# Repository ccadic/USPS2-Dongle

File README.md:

# USPS2-Dongle
ESP32S2 HID Keyboard Key
Still at prototype stage

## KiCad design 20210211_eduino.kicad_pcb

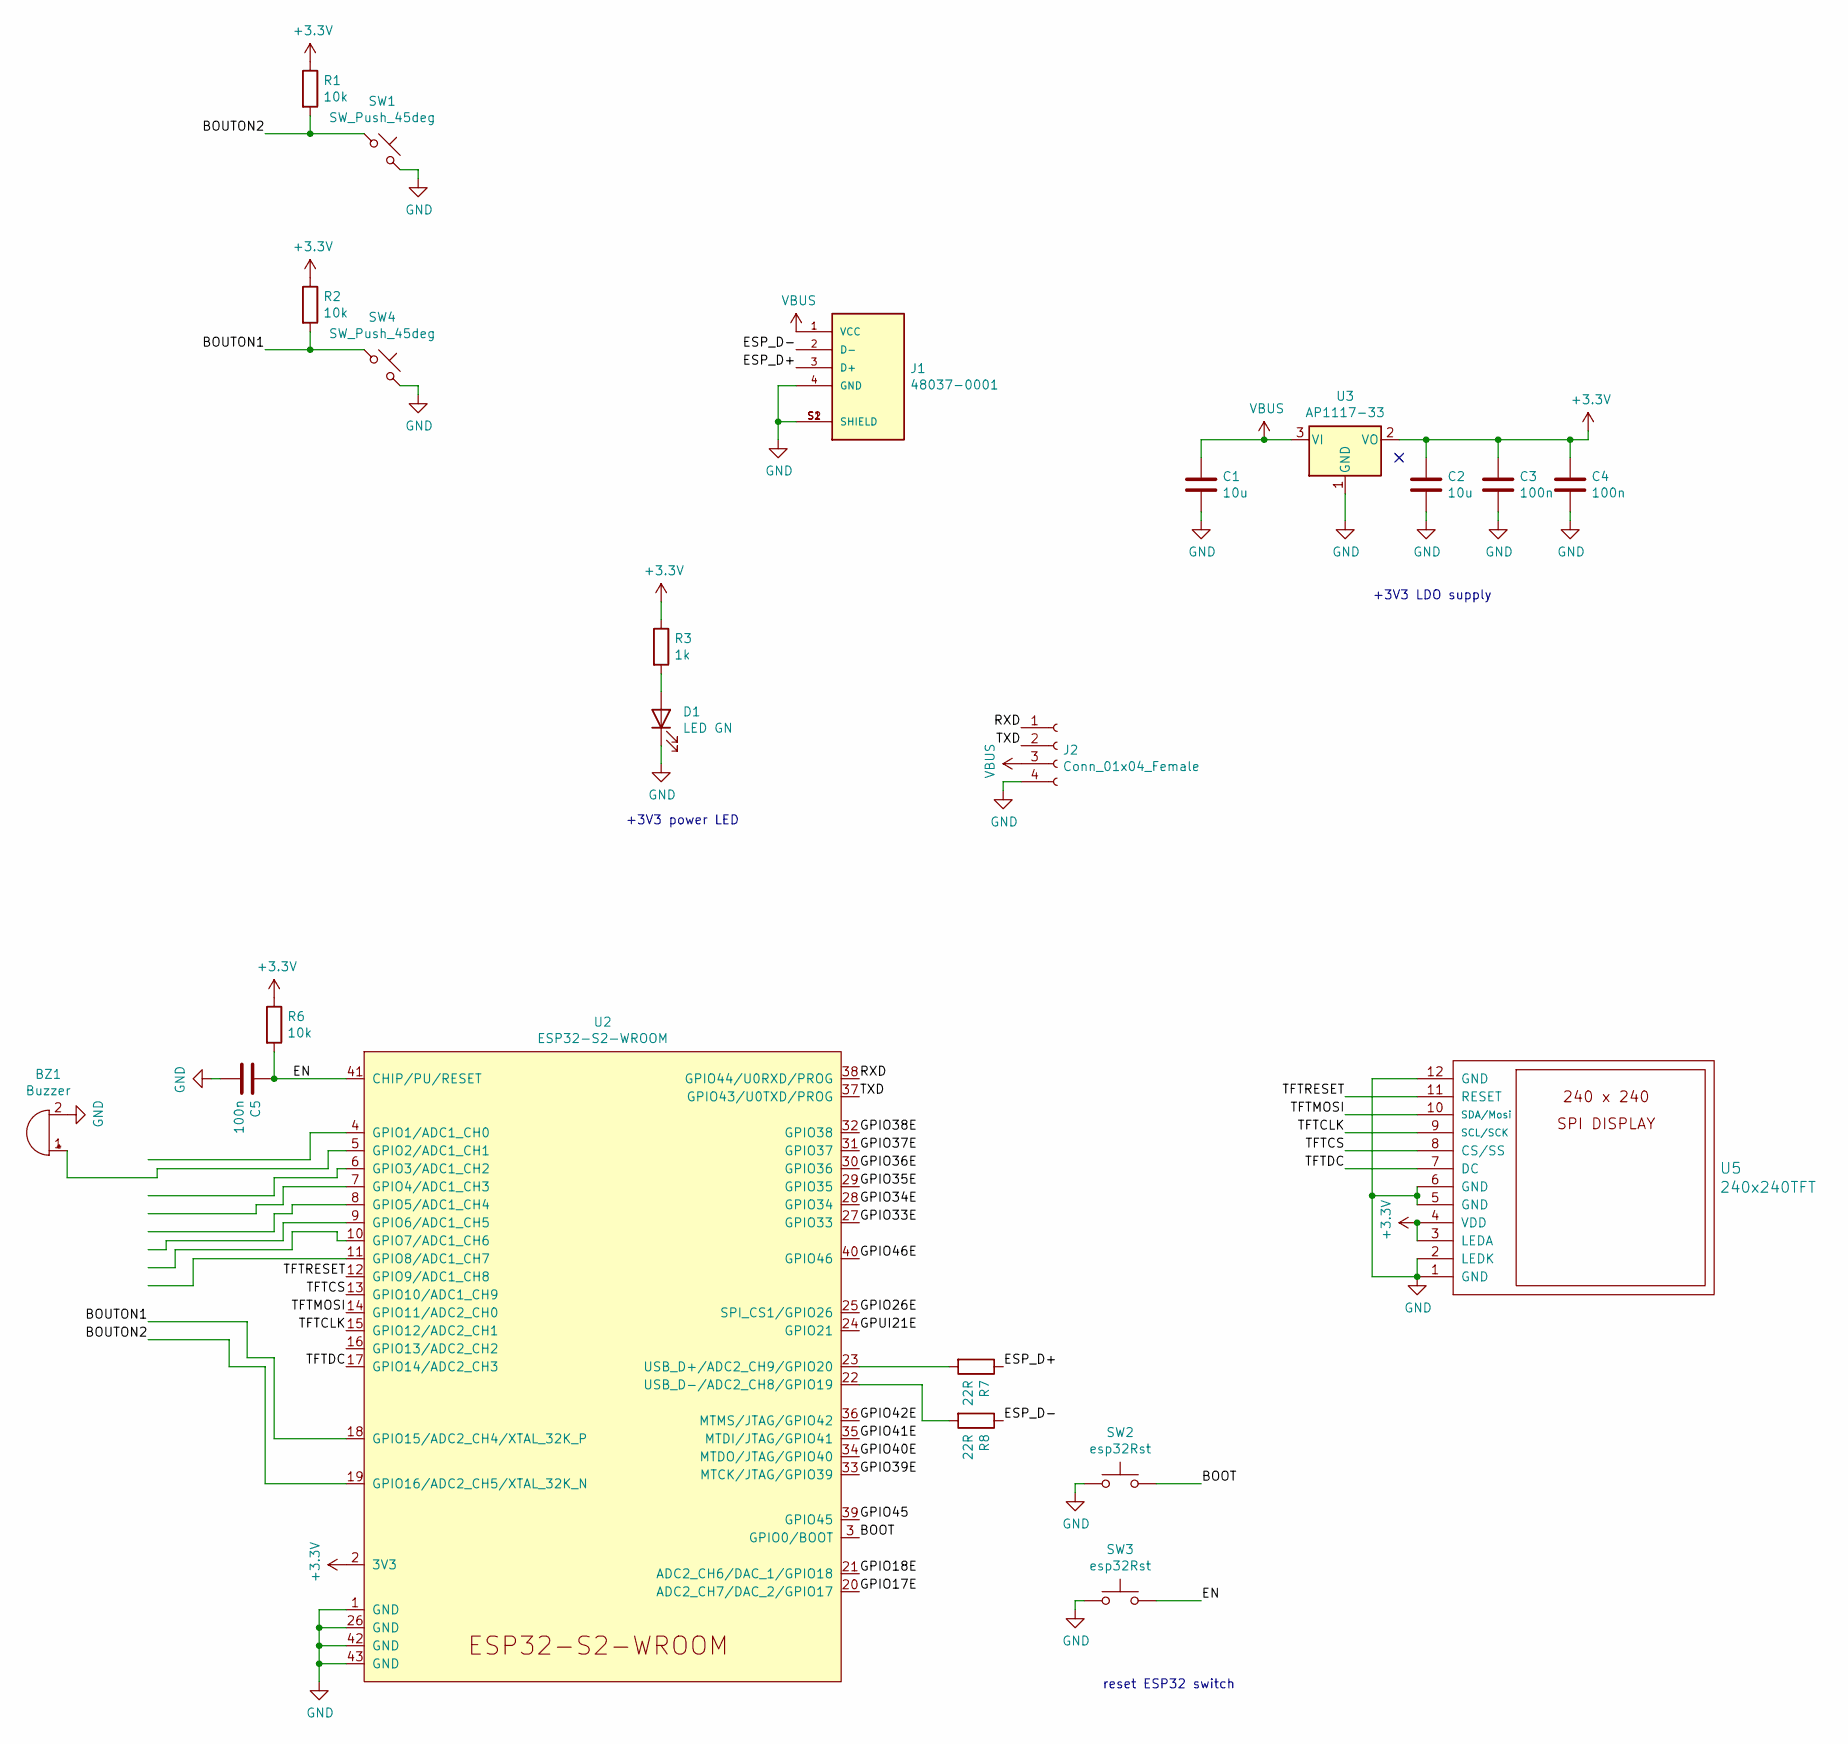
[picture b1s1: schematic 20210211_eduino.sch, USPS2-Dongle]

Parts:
BZ1: Buzzer; BuzzerActive2
C1, C2: 10u; C_0805
C3, C4: 100n; C_0805
C5: 100n; C_0603
D1: LED GN; LED_0603
J1: 48037-0001; MOLEX_48037-0001; PARTREV D
J2: Conn_01x04_Female; 4cnx
R1, R2, R6: 10k; R_0603
R3: 1k; R_0603
R7, R8: 22R; R_0603
SW1, SW4: SW_Push_45deg; SW_TP1003
SW2, SW3: esp32Rst; SW_SPST_B3U-1000P
U2: ESP32-S2-WROOM; esp32-s2-wrooom
U3: AP1117-33; SOT-223-3_TabPin2
U5: 240x240TFT; 240240TFT

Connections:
+3V3: C2.1, C3.1, C4.1, R1.1, R2.1, R3.1, R6.1, U2.2 (3V3), U3.2 (VO), U5.3 (LEDA), U5.4 (VDD)
/BOOT: SW2.2, U2.3 (GPIO0/BOOT)
/BOUTON1: R2.2, SW4.1, U2.18 (GPIO15/ADC2_CH4/XTAL_32K_P)
/BOUTON2: R1.2, SW1.1, U2.19 (GPIO16/ADC2_CH5/XTAL_32K_N)
/EN: C5.1, R6.2, SW3.2, U2.41 (CHIP/PU/RESET)
/ESP_D+: J1.3 (D+), R7.1
/ESP_D-: J1.2 (D-), R8.1
/GPIO17E: U2.20 (ADC2_CH7/DAC_2/GPIO17)
/GPIO18E: U2.21 (ADC2_CH6/DAC_1/GPIO18)
/GPIO26E: U2.25 (SPI_CS1/GPIO26)
/GPIO33E: U2.27 (GPIO33)
/GPIO34E: U2.28 (GPIO34)
/GPIO35E: U2.29 (GPIO35)
/GPIO36E: U2.30 (GPIO36)
/GPIO37E: U2.31 (GPIO37)
/GPIO38E: U2.32 (GPIO38)
/GPIO39E: U2.33 (MTCK/JTAG/GPIO39)
/GPIO40E: U2.34 (MTDO/JTAG/GPIO40)
/GPIO41E: U2.35 (MTDI/JTAG/GPIO41)
/GPIO42E: U2.36 (MTMS/JTAG/GPIO42)
/GPIO45: U2.39 (GPIO45)
/GPIO46E: U2.40 (GPIO46)
/GPUI21E: U2.24 (GPIO21)
/RXD: J2.1, U2.38 (GPIO44/U0RXD/PROG)
/TFTCLK: U2.15 (GPIO12/ADC2_CH1), U5.9 (SCL/SCK)
/TFTCS: U2.13 (GPIO10/ADC1_CH9), U5.8 (CS/SS)
/TFTDC: U2.17 (GPIO14/ADC2_CH3), U5.7 (DC)
/TFTMOSI: U2.14 (GPIO11/ADC2_CH0), U5.10 (SDA/Mosi)
/TFTRESET: U2.12 (GPIO9/ADC1_CH8), U5.11 (RESET)
/TXD: J2.2, U2.37 (GPIO43/U0TXD/PROG)
GND: BZ1.2 (+), C1.2, C2.2, C3.2, C4.2, C5.2, D1.1 (K), J1.4 (GND), J1.S1 (SHIELD), J1.S2 (SHIELD), J2.4, SW1.2, SW2.1, SW3.1, SW4.2, U2.1 (GND), U2.26 (GND), U2.42 (GND), U2.43 (GND), U3.1 (GND), U5.1 (GND), U5.2 (LEDK), U5.5 (GND), U5.6 (GND), U5.12 (GND)
unnamed: BZ1.1 (-), U2.5 (GPIO2/ADC1_CH1)
unnamed: D1.2 (A), R3.2
unnamed: R7.2, U2.23 (USB_D+/ADC2_CH9/GPIO20)
unnamed: R8.2, U2.22 (USB_D-/ADC2_CH8/GPIO19)
VBUS: C1.1, J1.1 (VCC), J2.3, U3.3 (VI)

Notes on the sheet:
+3V3 power LED
+3V3 LDO supply
reset ESP32 switch

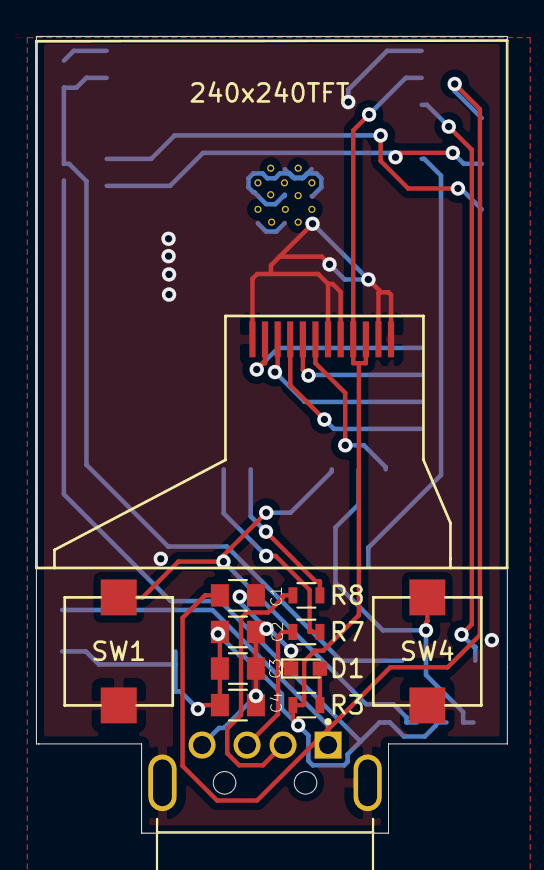
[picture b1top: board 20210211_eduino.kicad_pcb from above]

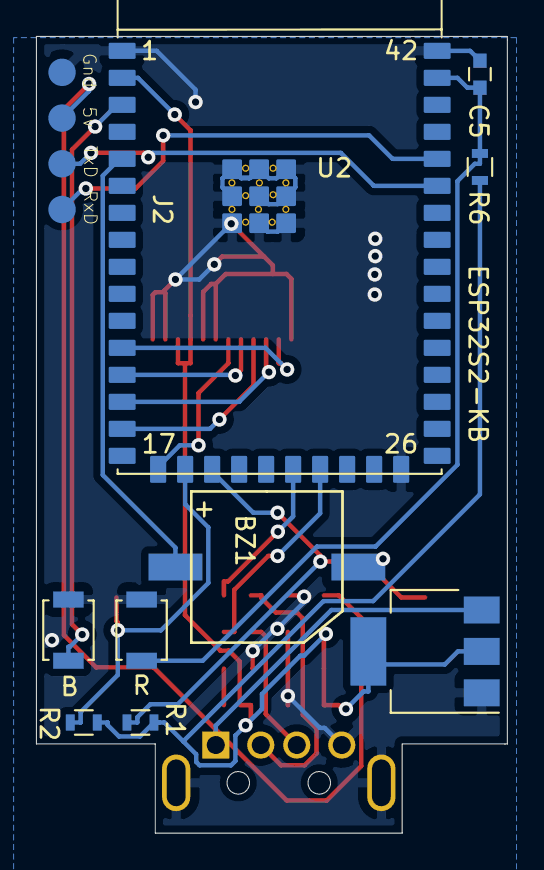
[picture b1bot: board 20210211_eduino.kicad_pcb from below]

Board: 2 copper layers, 26.2 x 44.3 mm, 22 parts (10 on the bottom side), 20 nets.
